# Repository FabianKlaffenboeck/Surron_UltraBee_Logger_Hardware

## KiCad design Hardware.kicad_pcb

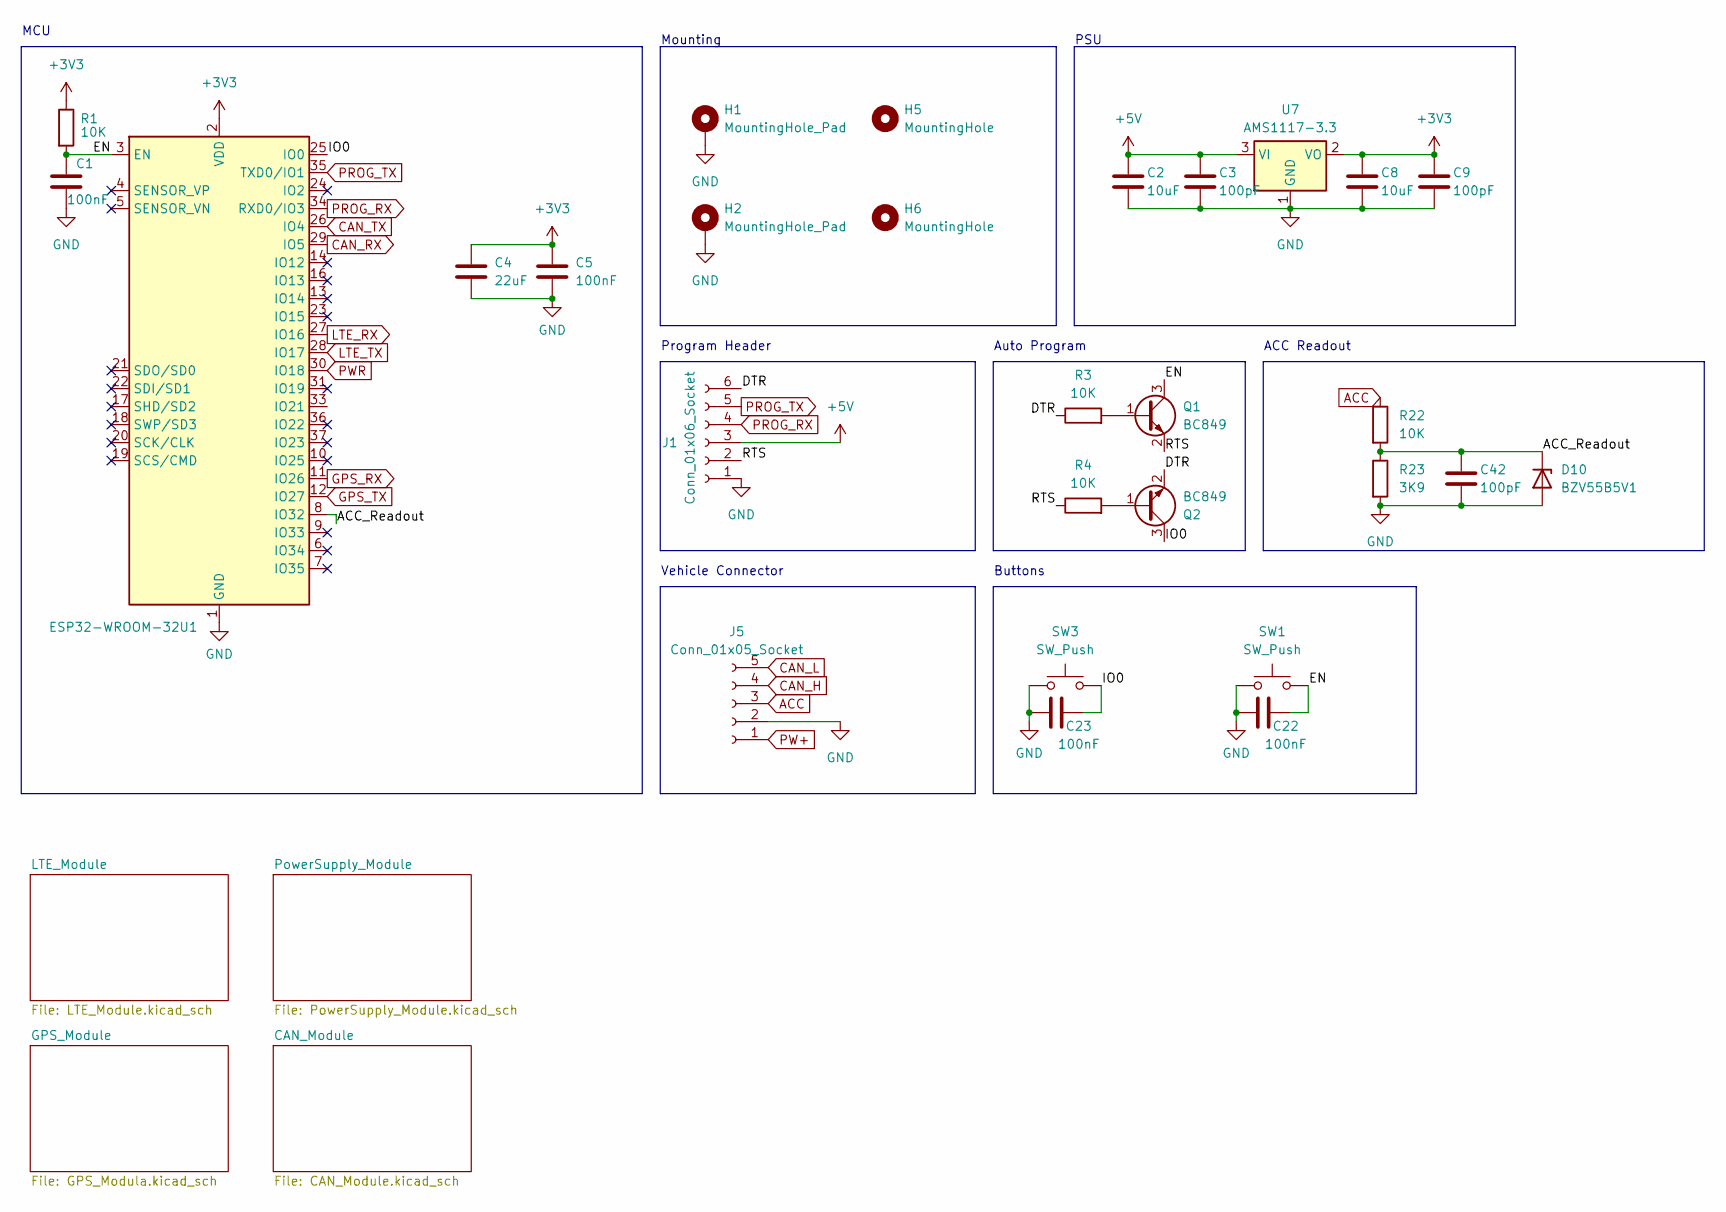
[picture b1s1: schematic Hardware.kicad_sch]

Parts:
C1, C5, C22, C23: 100nF; C_0805_2012Metric
C2, C8: 10uF; C_1206_3216Metric
C3, C9, C42: 100pF; C_0805_2012Metric
C4: 22uF; C_0603_1608Metric
D10: BZV55B5V1; D_MiniMELF
H1, H2: MountingHole_Pad; MountingHole_3.2mm_M3_DIN965_Pad
H5, H6: MountingHole; MountingHole_3.2mm_M3
J1: Conn_01x06_Socket; PinHeader_1x06_P2.54mm_Vertical
J5: Conn_01x05_Socket; PinHeader_1x05_P2.54mm_Vertical
Q1, Q2: BC849; SOT-23
R1, R3, R4, R22: 10K; R_0603_1608Metric
R23: 3K9; R_0603_1608Metric
SW1, SW3: SW_Push; SolderJumper-2_P1.3mm_Open_RoundedPad1.0x1.5mm
U1: ESP32-WROOM-32
U7: AMS1117-3.3; SOT-223-3_TabPin2

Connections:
+3V3: C4.1, C5.1, C8.1, C9.1, R1.1, U1.2 (VDD), U7.2 (VO); also elsewhere on the board
+5V: C2.1, C3.1, J1.3, U7.3 (VI); also elsewhere on the board
/ACC_Readout: C42.1, D10.1 (K), R22.2, R23.1, U1.8 (IO32)
/DTR: J1.6, Q2.2 (E), R3.1
/EN: C1.1, C22.2, Q1.3 (C), R1.2, SW1.2, U1.3 (EN)
/IO0: C23.2, Q2.3 (C), SW3.2, U1.25 (IO0)
/RTS: J1.2, Q1.2 (E), R4.1
ACC: J5.3, R22.1
CAN_H: J5.4; also elsewhere on the board
CAN_L: J5.5; also elsewhere on the board
CAN_RX: U1.29 (IO5); also elsewhere on the board
CAN_TX: U1.26 (IO4); also elsewhere on the board
GND: C1.2, C2.2, C3.2, C4.2, C5.2, C8.2, C9.2, C22.1, C23.1, C42.2, D10.2 (A), H1.1, H2.1, J1.1, J5.2, R23.2, SW1.1, SW3.1, U1.1 (GND), U1.15 (GND), U1.38 (GND), U1.39 (GND), U7.1 (GND); also elsewhere on the board
GPS_RX: U1.11 (IO26); also elsewhere on the board
GPS_TX: U1.12 (IO27); also elsewhere on the board
LTE_RX: U1.27 (IO16); also elsewhere on the board
LTE_TX: U1.28 (IO17); also elsewhere on the board
unnamed: Q1.1 (B), R3.2
unnamed: Q2.1 (B), R4.2
PROG_RX: J1.4, U1.34 (RXD0/IO3)
PROG_TX: J1.5, U1.35 (TXD0/IO1)
PW+: J5.1; also elsewhere on the board
PWR: U1.30 (IO18); also elsewhere on the board

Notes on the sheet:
Buttons
Auto Program
Vehicle Connector
PSU
Mounting
Program Header
MCU
ACC Readout

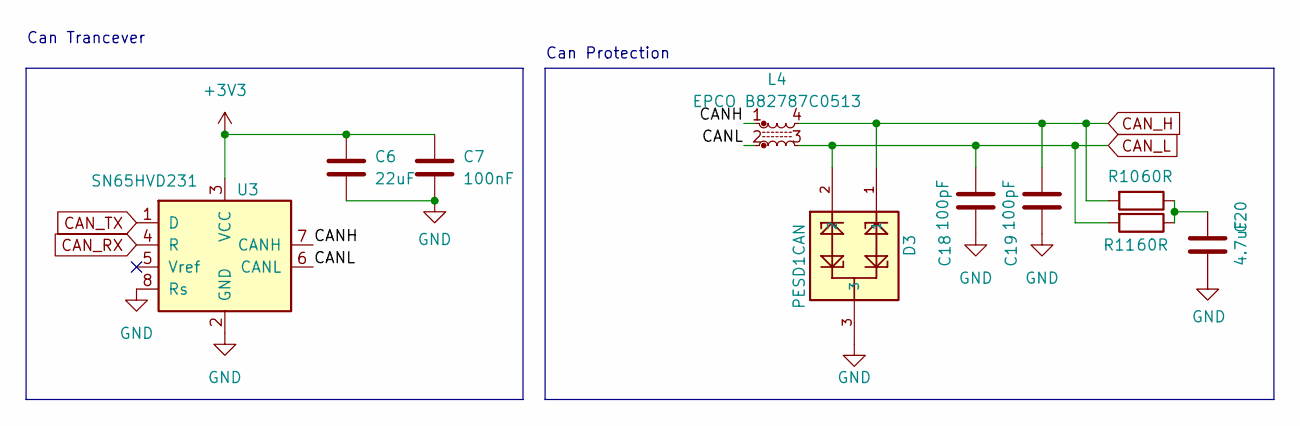
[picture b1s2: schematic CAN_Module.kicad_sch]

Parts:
C6: 22uF; C_0603_1608Metric
C7: 100nF; C_0805_2012Metric
C18, C19: 100pF; C_0805_2012Metric
C20: 4.7uF; C_0805_2012Metric
D3: PESD1CAN; SOT-23-3
L4: EPCO B82787C0513
R10, R11: 60R; R_0603_1608Metric
U3: SN65HVD231; SOIC-8_3.9x4.9mm_P1.27mm

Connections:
+3V3: C6.1, C7.1, U3.3 (VCC); also elsewhere on the board
/CAN_Module/CANH: L4.1, U3.7 (CANH)
/CAN_Module/CANL: L4.2, U3.6 (CANL)
CAN_H: C19.2, D3.1, L4.4, R10.2; also elsewhere on the board
CAN_L: C18.2, D3.2, L4.3, R11.2; also elsewhere on the board
CAN_RX: U3.4 (R); also elsewhere on the board
CAN_TX: U3.1 (D); also elsewhere on the board
GND: C6.2, C7.2, C18.1, C19.1, C20.2, D3.3, U3.2 (GND), U3.8 (Rs); also elsewhere on the board
unnamed: C20.1, R10.1, R11.1

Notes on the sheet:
Can Trancever
Can Protection

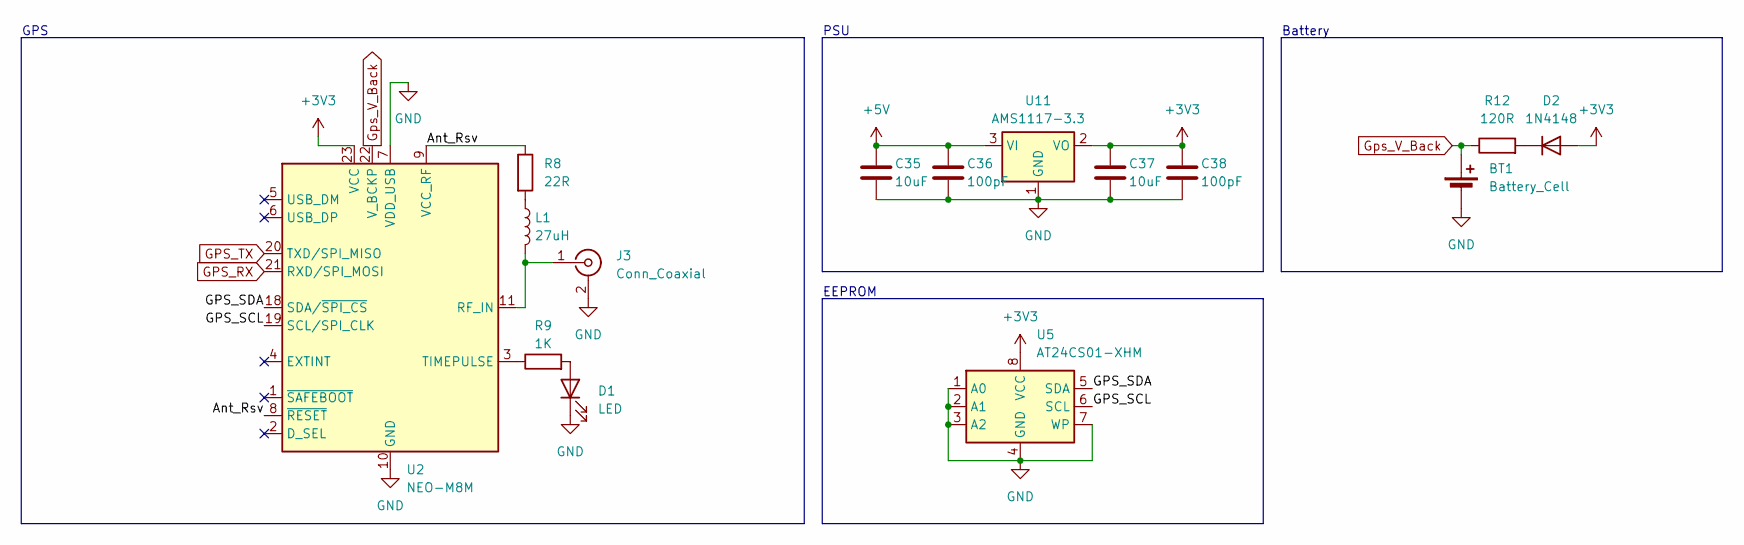
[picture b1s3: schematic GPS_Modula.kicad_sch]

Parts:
BT1: Battery_Cell; BatteryHolder_Seiko_MS621F
C35, C37: 10uF; C_1206_3216Metric
C36, C38: 100pF; C_0805_2012Metric
D1: LED; C_0603_1608Metric
D2: 1N4148; D_SOD-323
J3: Conn_Coaxial; U.FL_Molex_MCRF_73412-0110_Vertical
L1: 27uH; L_0805_2012Metric
R8: 22R; R_0603_1608Metric
R9: 1K; R_0603_1608Metric
R12: 120R; R_0603_1608Metric
U2: NEO-M8M; ublox_NEO
U5: AT24CS01-XHM; TSSOP-8_4.4x3mm_P0.65mm
U11: AMS1117-3.3; SOT-223-3_TabPin2

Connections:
+3V3: C37.1, C38.1, D2.2 (A), U2.23 (VCC), U5.8 (VCC), U11.2 (VO); also elsewhere on the board
+5V: C35.1, C36.1, U11.3 (VI); also elsewhere on the board
/GPS_Module/Ant_Rsv: R8.1, U2.8 (~RESET), U2.9 (VCC_RF)
/GPS_Module/GPS_SCL: U2.19 (SCL/SPI_CLK), U5.6 (SCL)
/GPS_Module/GPS_SDA: U2.18 (SDA/~SPI_CS), U5.5 (SDA)
GND: BT1.2 (-), C35.2, C36.2, C37.2, C38.2, D1.1 (K), J3.2 (Ext), U2.7 (VDD_USB), U2.10 (GND), U2.12 (GND), U2.13 (GND), U2.24 (GND), U5.1 (A0), U5.2 (A1), U5.3 (A2), U5.4 (GND), U5.7 (WP), U11.1 (GND); also elsewhere on the board
GPS_RX: U2.21 (RXD/SPI_MOSI); also elsewhere on the board
GPS_TX: U2.20 (TXD/SPI_MISO); also elsewhere on the board
Gps_V_Back: BT1.1 (+), R12.1, U2.22 (V_BCKP)
unnamed: D1.2 (A), R9.2
unnamed: D2.1 (K), R12.2
unnamed: J3.1 (In), L1.2, U2.11 (RF_IN)
unnamed: L1.1, R8.2
unnamed: R9.1, U2.3 (TIMEPULSE)

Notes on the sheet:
EEPROM
Battery
PSU
GPS

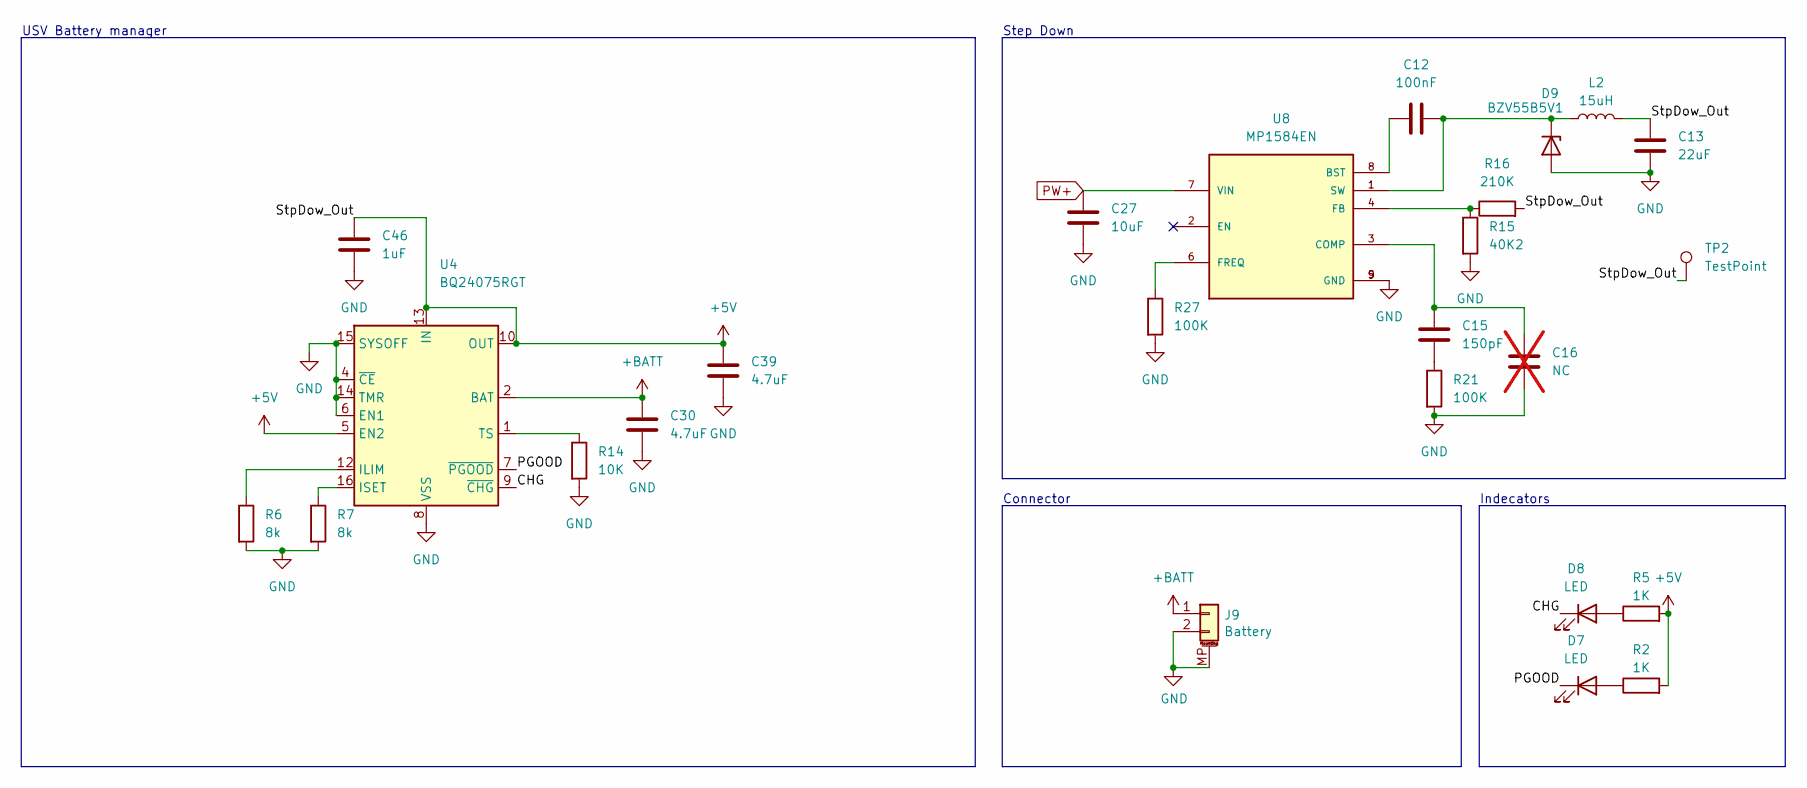
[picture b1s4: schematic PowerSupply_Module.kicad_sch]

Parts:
C12: 100nF; C_0805_2012Metric
C13: 22uF; C_0603_1608Metric
C15: 150pF; C_0603_1608Metric
C16: NC; C_0805_2012Metric; not fitted
C27: 10uF; C_1206_3216Metric
C30, C39: 4.7uF; C_0805_2012Metric
C46: 1uF; C_0603_1608Metric
D7, D8: LED; C_0603_1608Metric
D9: BZV55B5V1; D_MiniMELF
J9: Battery; JST_PH_S2B-PH-SM4-TB_1x02-1MP_P2.00mm_Horizontal
L2: 15uH; L_Abracon_ASPI-0630LR
R2, R5: 1K; R_0603_1608Metric
R6, R7: 8k; R_0603_1608Metric
R14: 10K; R_0603_1608Metric
R15: 40K2; R_0603_1608Metric
R16: 210K; R_0603_1608Metric
R21, R27: 100K; R_0603_1608Metric
TP2: TestPoint; TestPoint_Pad_D1.5mm
U4: BQ24075RGT; VQFN-16-1EP_3x3mm_P0.5mm_EP1.6x1.6mm
U8: MP1584EN; SOIC127P600X170-9N

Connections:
+5V: C13.1, C39.1, C46.1, L2.2, R2.2, R5.2, R16.2, TP2.1, U4.5 (EN2), U4.10 (OUT), U4.11 (OUT), U4.13 (IN); also elsewhere on the board
+BATT: C30.1, J9.1, U4.2 (BAT), U4.3 (BAT)
/PowerSupply_Module/CHG: D8.1 (K), U4.9 (~CHG)
/PowerSupply_Module/PGOOD: D7.1 (K), U4.7 (~PGOOD)
GND: C13.2, C16.1, C27.1, C30.2, C39.2, C46.2, D9.2 (A), J9.2, J9.MP (MountPin), R6.2, R7.2, R14.2, R15.2, R21.2, R27.2, U4.4 (~CE), U4.6 (EN1), U4.8 (VSS), U4.14 (TMR), U4.15 (SYSOFF), U4.17 (VSS), U8.5 (GND), U8.9 (GND); also elsewhere on the board
unnamed: C15.1, R21.1
unnamed: D7.2 (A), R2.1
unnamed: D8.2 (A), R5.1
unnamed: C12.2, D9.1 (K), L2.1, U8.1 (SW)
unnamed: R6.1, U4.12 (ILIM)
unnamed: R7.1, U4.16 (ISET)
unnamed: R14.1, U4.1 (TS)
unnamed: C12.1, U8.8 (BST)
unnamed: C15.2, C16.2, U8.3 (COMP)
unnamed: R15.1, R16.1, U8.4 (FB)
unnamed: R27.1, U8.6 (FREQ)
PW+: C27.2, U8.7 (VIN); also elsewhere on the board

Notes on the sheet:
USV Battery manager
Step Down
Connector
Indecators

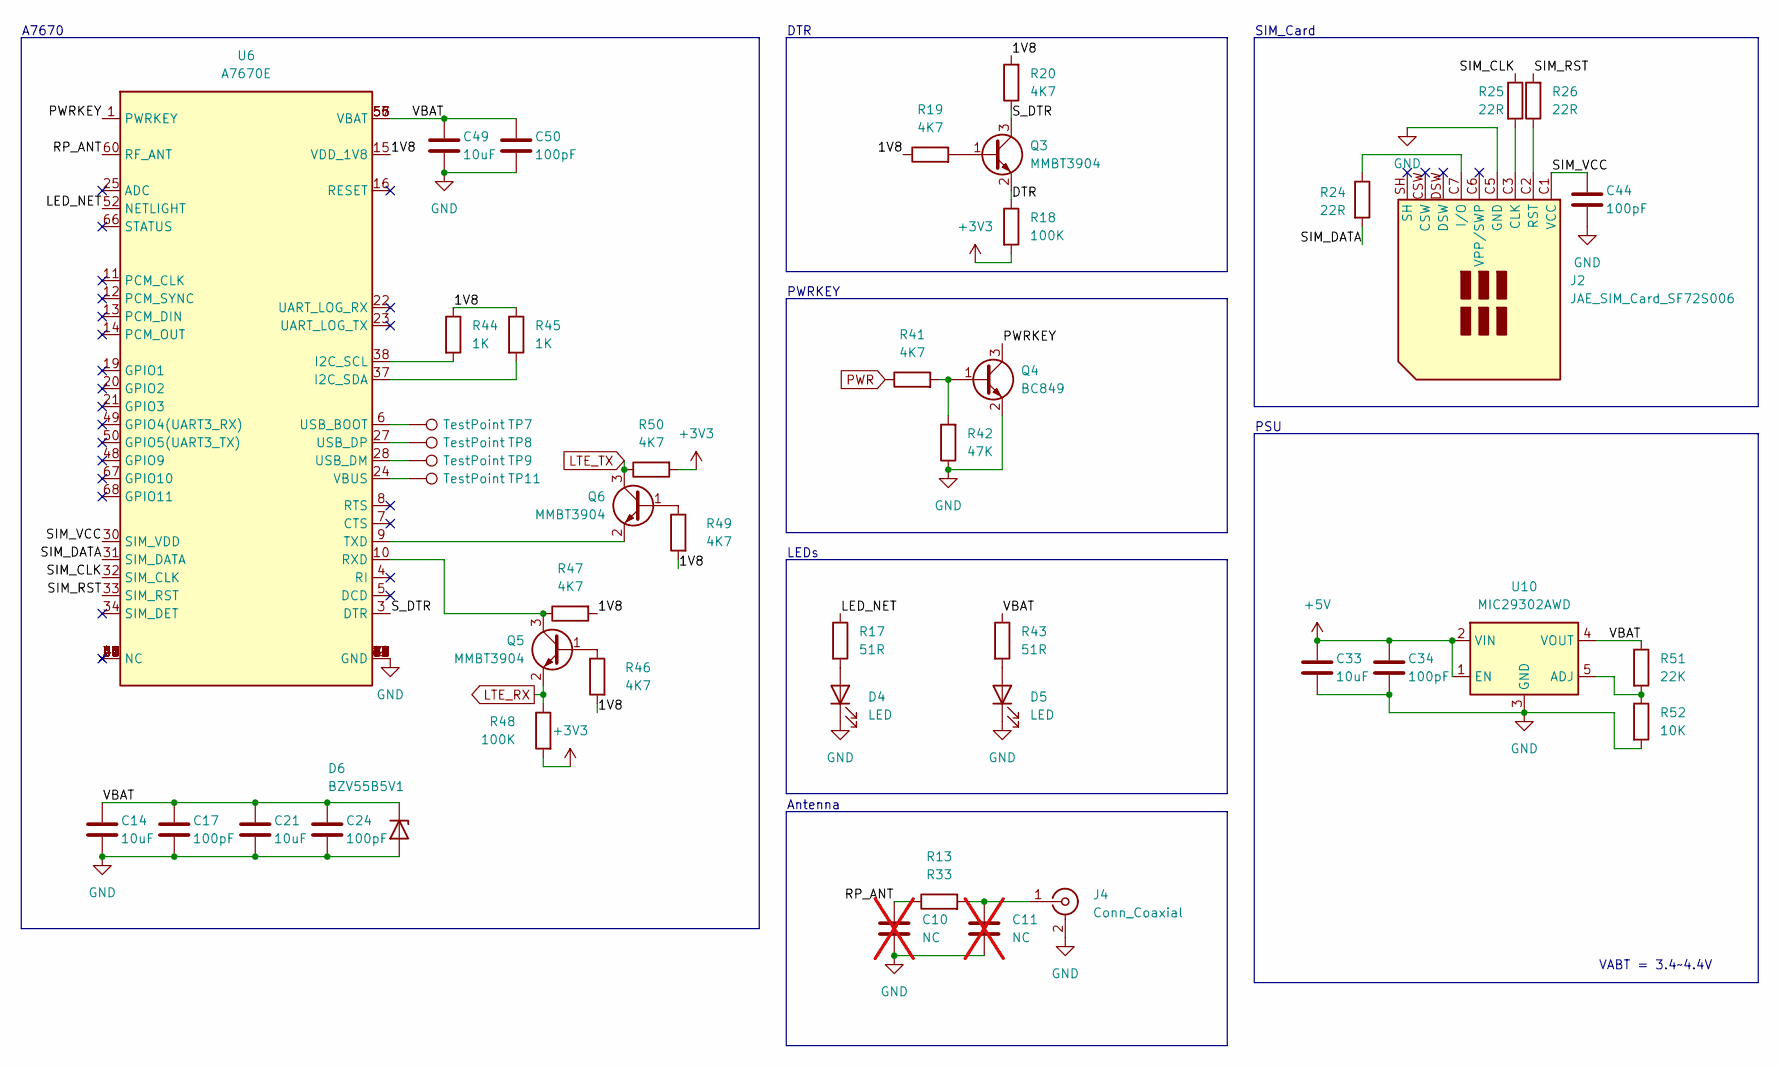
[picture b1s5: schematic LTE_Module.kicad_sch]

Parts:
C10, C11: NC; C_0805_2012Metric; not fitted
C14, C21, C33, C49: 10uF; C_1206_3216Metric
C17, C24, C34, C44, C50: 100pF; C_0805_2012Metric
D4, D5: LED; C_0603_1608Metric
D6: BZV55B5V1; D_MiniMELF
J2: JAE_SIM_Card_SF72S006
J4: Conn_Coaxial; U.FL_Molex_MCRF_73412-0110_Vertical
Q3, Q5, Q6: MMBT3904; SOT-23
Q4: BC849; SOT-23
R13: R33; R_0603_1608Metric
R17, R43: 51R; R_0603_1608Metric
R18, R48: 100K; R_0603_1608Metric
R19, R20, R41, R46, R47, R49, R50: 4K7; R_0603_1608Metric
R24, R25, R26: 22R; R_0603_1608Metric
R42: 47K; R_0603_1608Metric
R44, R45: 1K; R_0603_1608Metric
R51: 22K; R_0603_1608Metric
R52: 10K; R_0603_1608Metric
TP7, TP8, TP9, TP11: TestPoint; TestPoint_Pad_D1.5mm
U6: A7670E
U10: MIC29302AWD; TO-252-5_TabPin3

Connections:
+3V3: R18.2, R48.2, R50.2; also elsewhere on the board
+5V: C33.1, C34.1, U10.1 (EN), U10.2 (VIN); also elsewhere on the board
/LTE_Module/1V8: R19.1, R20.2, R44.1, R45.1, R46.2, R47.2, R49.2, U6.15 (VDD_1V8)
/LTE_Module/DTR: Q3.2 (E), R18.1
/LTE_Module/LED_NET: R17.1, U6.52 (NETLIGHT)
/LTE_Module/PWRKEY: Q4.3 (C), U6.1 (PWRKEY)
/LTE_Module/RP_ANT: C10.1, R13.1, U6.60 (RF_ANT)
/LTE_Module/SIM_CLK: R25.1, U6.32 (SIM_CLK)
/LTE_Module/SIM_DATA: R24.2, U6.31 (SIM_DATA)
/LTE_Module/SIM_RST: R26.2, U6.33 (SIM_RST)
/LTE_Module/SIM_VCC: C44.1, J2.C1 (VCC), U6.30 (SIM_VDD)
/LTE_Module/S_DTR: Q3.3 (C), R20.1, U6.3 (DTR)
/LTE_Module/VBAT: C14.1, C17.1, C21.1, C24.1, C49.1, C50.1, D6.1 (K), R43.1, R51.1, U6.55 (VBAT), U6.56 (VBAT), U6.57 (VBAT), U10.4 (VOUT)
GND: C10.2, C11.2, C14.2, C17.2, C21.2, C24.2, C33.2, C34.2, C44.2, C49.2, C50.2, D4.1 (K), D5.1 (K), D6.2 (A), J2.C5 (GND), J4.2 (Ext), Q4.2 (E), R42.1, R52.2, U6.2 (GND), U6.17 (GND), U6.18 (GND), U6.29 (GND), U6.39 (GND), U6.45 (GND), U6.46 (GND), U6.54 (GND), U6.58 (GND), U6.59 (GND), U6.61 (GND), U6.62 (GND), U6.63 (GND), U6.64 (GND), U6.65 (GND), U6.69 (GND), U6.70 (GND), U6.71 (GND), U6.72 (GND), U6.73 (GND), U6.74 (GND), U6.75 (GND), U6.76 (GND), U6.77 (GND), U6.78 (GND), U6.79 (GND), U6.80 (GND), U6.81 (GND), U6.82 (GND), U6.83 (GND), U6.84 (GND), U6.85 (GND), U6.86 (GND), U6.87 (GND), U6.88 (GND), U10.3 (GND); also elsewhere on the board
LTE_RX: Q5.2 (E), R48.1; also elsewhere on the board
LTE_TX: Q6.3 (C), R50.1; also elsewhere on the board
unnamed: D4.2 (A), R17.2
unnamed: D5.2 (A), R43.2
unnamed: J2.C3 (CLK), R25.2
unnamed: J2.C7 (I/O), R24.1
unnamed: J2.C2 (RST), R26.1
unnamed: C11.1, J4.1 (In), R13.2
unnamed: Q3.1 (B), R19.2
unnamed: Q4.1 (B), R41.2, R42.2
unnamed: Q5.1 (B), R46.1
unnamed: Q5.3 (C), R47.1, U6.10 (RXD)
unnamed: Q6.1 (B), R49.1
unnamed: Q6.2 (E), U6.9 (TXD)
unnamed: R44.2, U6.38 (I2C_SCL)
unnamed: R45.2, U6.37 (I2C_SDA)
unnamed: TP7.1, U6.6 (USB_BOOT)
unnamed: TP9.1, U6.28 (USB_DM)
unnamed: TP8.1, U6.27 (USB_DP)
unnamed: TP11.1, U6.24 (VBUS)
unnamed: R51.2, R52.1, U10.5 (ADJ)
PWR: R41.1; also elsewhere on the board

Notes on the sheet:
PWRKEY
A7670
DTR
PSU
LEDs
SIM_Card
Antenna
VABT = 3.4~4.4V

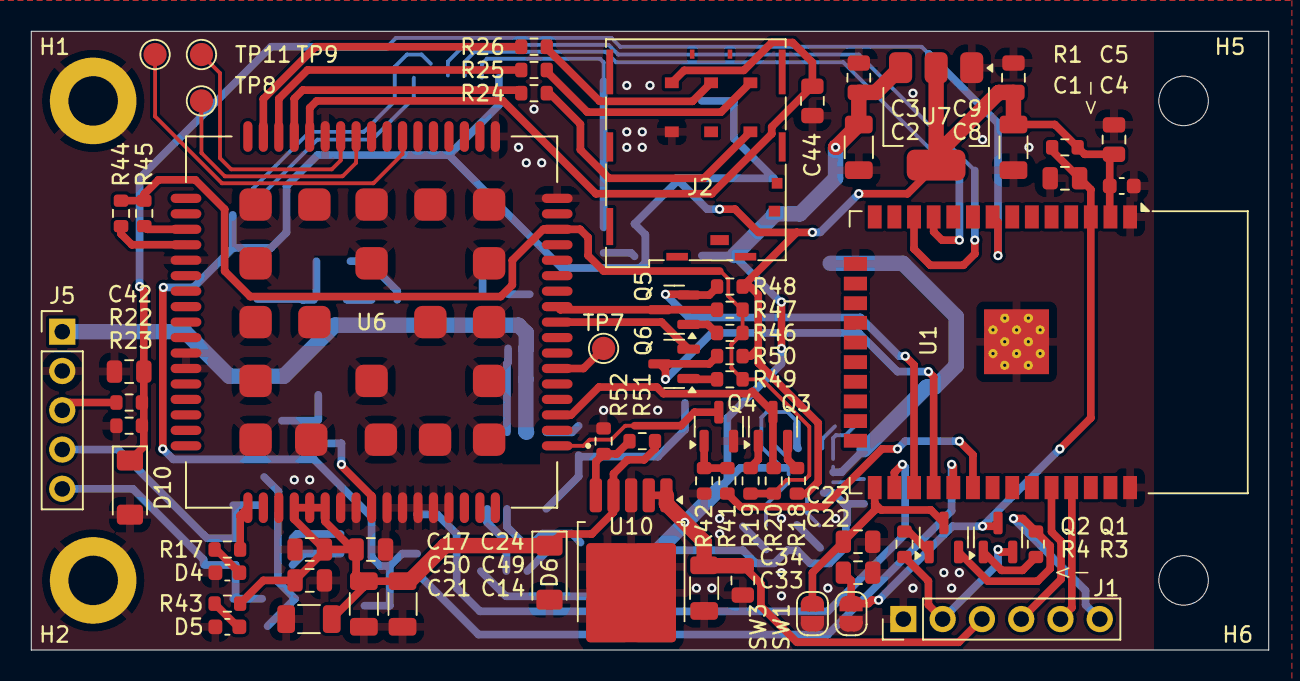
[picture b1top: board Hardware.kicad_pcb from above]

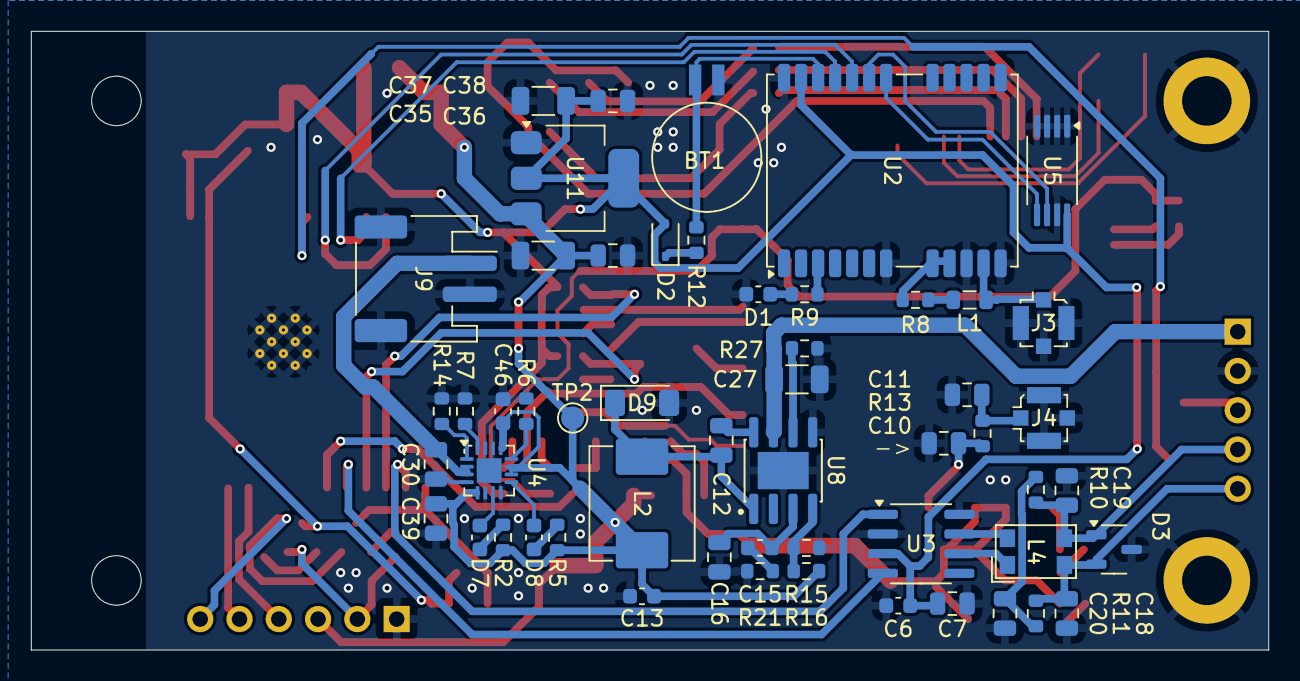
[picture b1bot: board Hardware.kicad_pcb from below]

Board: 2 copper layers, 80.0 x 40.0 mm, 124 parts (54 on the bottom side), 79 nets.

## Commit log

2024-04-01 added files for Kibot
2024-04-01 fixed repo
2024-04-01 updated cicd
2024-04-05 added scematics for gps and sd reader
2024-04-05 removed vscore stuff
2024-04-07 mostly finisged scematics
2024-04-09 done some layouting
2024-04-09 added testpoints
2024-04-10 moved everythint into hirachical sheets
2024-04-10 fixed layout
2024-04-10 added psu and formated board outline
2024-04-10 added charging footprint
2024-04-11 added power layout
2024-04-11 added step down
2024-05-07 dry cicd
2024-05-15 added fooptint for sim7070
2024-05-15 added footprint for a7670e
2024-05-20 done most of the schematics
2024-05-20 done refacoring
2024-05-28 assigned most footprints
2024-05-31 cleaned up scematics and updated power management
2024-05-31 finelized scematics
2024-06-01 mostly layouted
2024-06-01 pre remobing sd card
2024-06-02 mostly finished layout
2024-06-23 switchen can supply to 3v3
2024-06-30 updated schematics:
    Fixed bug with PWKEY of LTE module
    Fixed big with power
2024-07-02 first new layout
2024-07-02 cleaned up
2024-07-02 cleaned silkscreen
2024-07-02 fixed drc
2024-08-03 cahnged resistor value for charing current
2024-08-03 updated cicd location
2024-09-11 Add LICENSE
2024-09-11 Update .gitlab-ci.yml file
2025-04-21 Edit LICENSE
